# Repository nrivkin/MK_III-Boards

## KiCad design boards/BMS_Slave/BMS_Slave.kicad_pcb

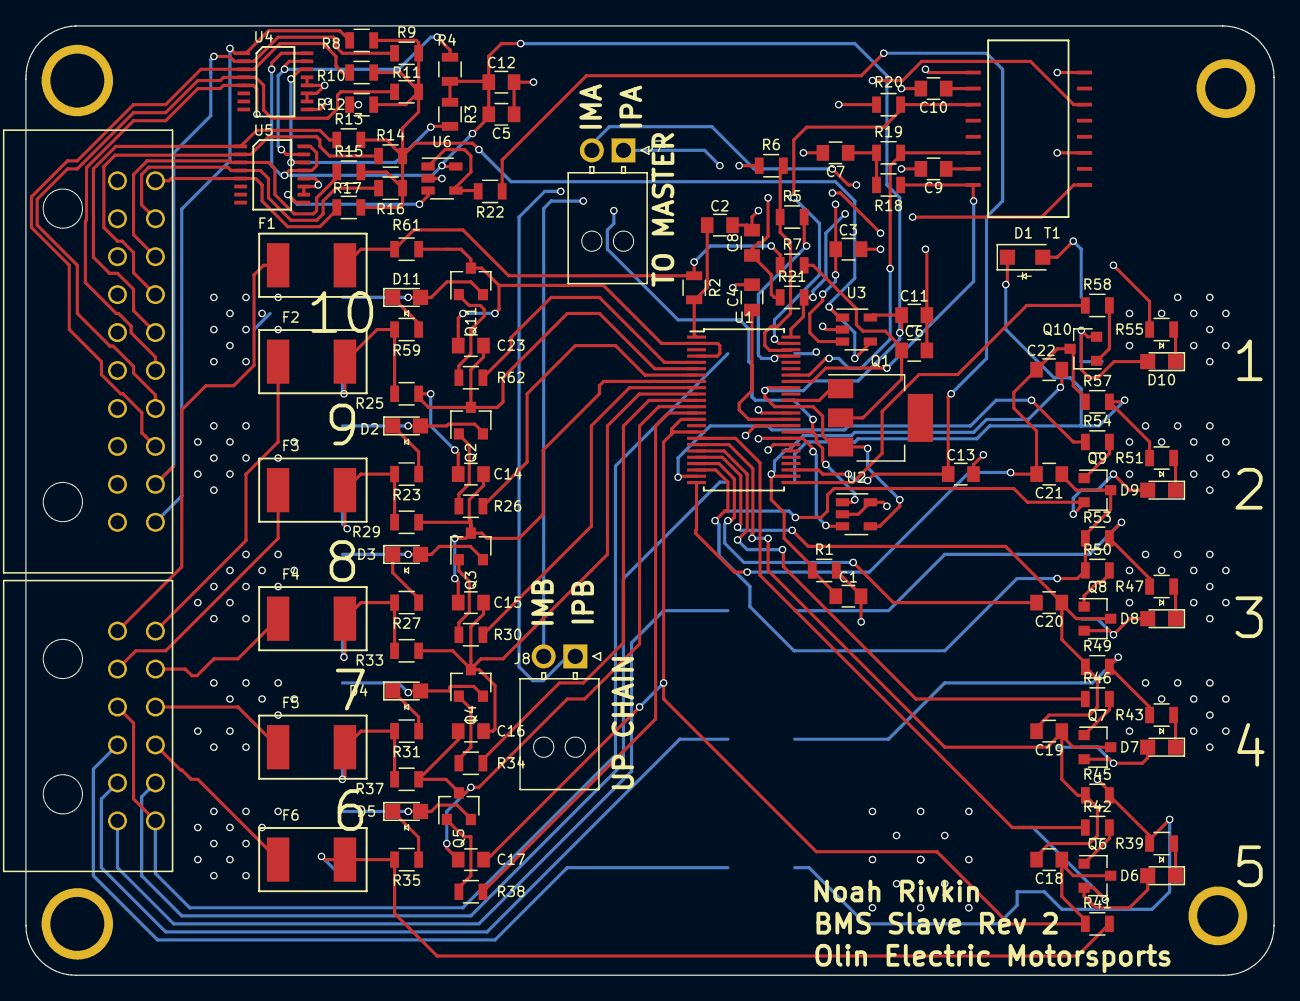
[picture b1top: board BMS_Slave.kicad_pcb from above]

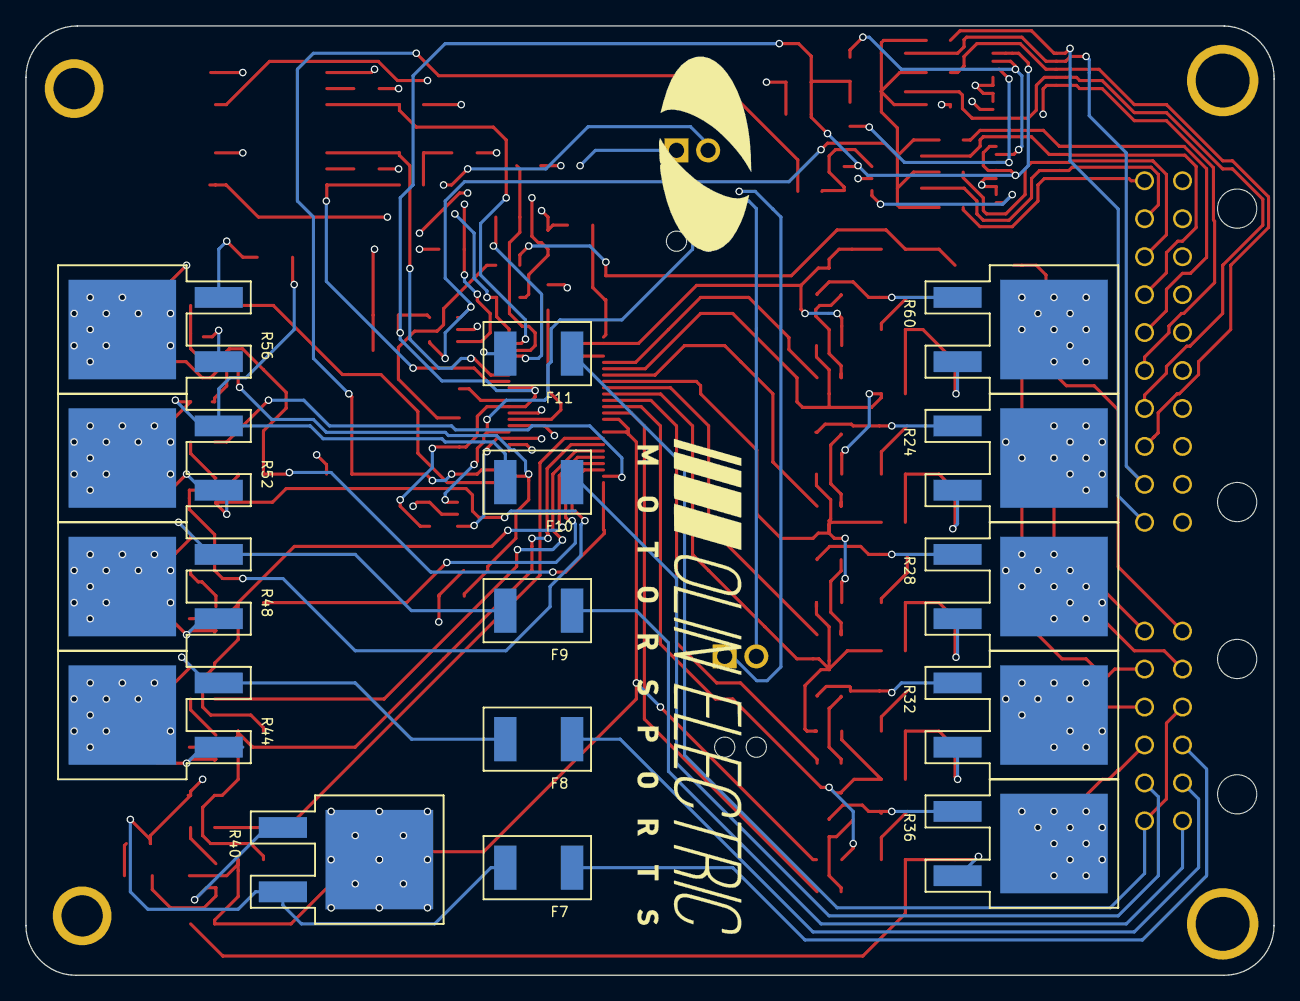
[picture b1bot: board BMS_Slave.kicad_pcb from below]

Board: 4 copper layers, 98.7 x 75.1 mm, 133 parts (15 on the bottom side), 109 nets.

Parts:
C1, C7, C8, C9, C10, C13, C14, C15, C16, C17, C18, C19, C20, C21, C22, C23: 10nF; C_0805_OEM
C2, C6: C_0.1uF; C_0805_OEM
C3, C4, C5, C11, C12: 1uF; C_0805_OEM
D1: D_Schottky_SOD123; D_SOD-123W_OEM
D2, D3, D4, D5, D6, D7, D8, D9, D10, D11: LED_0805; LED_0805_OEM
F1, F2, F3, F4, F5, F6, F7, F8, F9, F10, F11: 200mA_Fuse; Fuse_1812
J1, J3: Mounting_Hole_4-40
J2, J4: Mounting_Hole_4-40; Mounting_Hole_Insert_4-40
J5: MicroFit_12; Microfit3_Header_02x06_Angled_OEM
J6: MicroFit_20; Molex_Microfit3_Header_02x10_Angled_OEM
J7, J8: NanoFit_2; Molex_NanoFit_1x02x2.50mm_Angled_OEM
Q1: Q_NPN_BCE; SOT-223
Q2, Q3, Q4, Q5, Q6, Q7, Q8, Q9, Q10, Q11: NMOS_GSD_30V; SOT-23F
R1, R2, R7, R22, R25, R29, R33, R37, R41, R45, R49, R53, R57, R61: R_100; R_0805_OEM
R3, R4: 4.99k; R_0805_OEM
R5, R6: R_1k; R_0805_OEM
R8, R9, R10, R11, R12, R13, R14, R15, R16, R17: R_10k; R_0805_OEM
R18, R19, R20, R21: 60.4; R_0805_OEM
R23, R27, R31, R35, R39, R43, R47, R51, R55, R59: R_475; R_0805_OEM
R24, R28, R32, R36, R40, R44, R48, R52, R56, R60: DTO25
R26, R30, R34, R38, R42, R46, R50, R54, R58, R62: 3.3k; R_0805_OEM
T1: T_LAN_7490100111A; 7490100111A
U1: LTC6811-1; TSSOP-48_LTC6811-1
U2: 24AA01; SOT-23-5_OEM
U3, U6: MCP6001; SOT-23-5_OEM
U4, U5: LTC1380; SSOP-16_LTC1380

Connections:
/Balance1/CELL_SENSE: C21.2, C22.1, Q10.3, R57.1, U1.24
/Balance1/SENSE_BELOW: C1.1, C22.2, R1.1, U1.26
/Balance2/CELL_SENSE: C21.1, Q9.3, R50.1, R53.1, U1.22
/Balance2/V_BELOW: D1.1, F10.2, R51.2, R52.2, R57.2
/Balance3/CELL_SENSE: C19.2, C20.1, Q8.3, R49.1, U1.20
/Balance3/V_BELOW: F9.2, R47.2, R48.2, R53.2
/Balance4/CELL_SENSE: C18.2, C19.1, Q7.3, R45.1, U1.18
/Balance4/V_BELOW: F8.2, R43.2, R44.2, R49.2
/Balance5/CELL_SENSE: C17.2, C18.1, Q6.3, R41.1, U1.14, U1.16
/Balance5/V_BELOW: F7.2, R39.2, R40.2, R45.2
/Balance6/CELL_SENSE: C16.2, C17.1, Q5.3, R37.1, U1.12
/Balance6/V_BELOW: F6.2, R35.2, R36.2, R41.2
/Balance7/CELL_SENSE: C15.2, C16.1, Q4.3, R33.1, U1.10
/Balance7/V_BELOW: F5.2, R31.2, R32.2, R37.2
/Balance8/CELL_SENSE: C14.2, C15.1, Q3.3, R29.1, U1.8
/Balance8/V_BELOW: F4.2, R27.2, R28.2, R33.2
/Balance9/CELL_SENSE: C14.1, C23.2, Q2.3, R25.1, U1.6
/Balance9/V_BELOW: F3.2, R23.2, R24.2, R29.2
/Balance10/CELL_SENSE: C23.1, Q11.3, R61.1, U1.2, U1.4
/Balance10/V_BELOW: F2.2, R25.2, R59.2, R60.2
/Balance10/V_CELL: F1.2, R2.1, R7.1, R61.2
/CELL_TEMP1: J6.11, R8.1, U4.1
/CELL_TEMP2: J6.12, R9.1, U4.2
/CELL_TEMP3: J6.13, R10.1, U4.3
/CELL_TEMP4: J6.14, R11.1, U4.4
/CELL_TEMP5: J6.15, R12.1, U4.5
/CELL_TEMP6: J6.16, R13.1, U5.1
/CELL_TEMP7: J6.17, R14.1, U5.2
/CELL_TEMP8: J6.18, R15.1, U5.3
/CELL_TEMP9: J6.19, R16.1, U5.4
/CELL_TEMP10: J6.20, R17.1, U5.5
/Cell1: F10.1, J5.8
/Cell2: F9.1, J5.1
/Cell3: F8.1, J5.2
/Cell4: F7.1, J5.3
/Cell5: F6.1, J5.9
/Cell6: F5.1, J5.10
/Cell7: F4.1, J5.11
/Cell8: F3.1, J5.5
/Cell9: F2.1, J5.12
/Cell10: F1.1, J5.6
/Control1: R58.1, U1.25
/Control2: R54.1, U1.23
/Control3: C20.2, U1.21
/Control4: R46.1, U1.19
/Control5: R42.1, U1.17
/Control6: R38.1, U1.13
/Control7: R34.1, U1.11
/Control8: R30.1, U1.9
/Control9: R26.1, U1.7
/Control10: R62.1, U1.5
/GPIO1: C13.1, R22.1, U1.27
/LowSide: F11.1, J5.4, J5.7
/SCL: R4.2, U1.33, U2.1, U4.15, U5.15
/SDA: R3.2, U1.32, U2.3, U4.14, U5.14
/VREF2: R8.2, R9.2, R10.2, R11.2, R12.2, R13.2, R14.2, R15.2, R16.2, R17.2, U3.1, U3.4
/VREG: C5.1, C11.1, C12.1, Q1.3, R3.1, R4.1, U1.37, U1.40, U2.4, U3.5, U4.16, U5.13, U5.16, U6.5
GND: C1.2, C2.2, C3.2, C4.2, C5.2, C6.2, C7.2, C8.2, C9.2, C10.2, C11.2, C12.2, C13.2, D1.2, F11.2, J6.1, J6.2, J6.3, J6.4, J6.5, J6.6, J6.7, J6.8, J6.9, J6.10, R1.2, R6.1, R55.2, R56.2, U1.30, U1.31, U1.36, U2.2, U2.5, U3.2, U4.10, U4.11, U4.12, U4.13, U5.10, U5.11, U5.12, U6.2
unnamed: C2.1, R2.2, U1.1
unnamed: C3.1, U1.34, U3.3
unnamed: C4.1, U1.35
unnamed: C6.1, Q1.2, R7.2
unnamed: C7.1, R18.2, R19.1
unnamed: C8.1, R20.2, R21.1
unnamed: C9.1, T1.15
unnamed: C10.1, T1.10
unnamed: D2.1, R23.1
unnamed: D2.2, Q2.2, R24.3
unnamed: D3.1, R27.1
unnamed: D3.2, Q3.2, R28.3
unnamed: D4.1, R31.1
unnamed: D4.2, Q4.2, R32.3
unnamed: D5.1, R35.1
unnamed: D5.2, Q5.2, R36.3
unnamed: D6.1, R39.1
unnamed: D6.2, Q6.2, R40.3
unnamed: D7.1, R43.1
unnamed: D7.2, Q7.2, R44.3
unnamed: D8.1, R47.1
unnamed: D8.2, Q8.2, R48.3
unnamed: D9.1, R51.1
unnamed: D9.2, Q9.2, R52.3
unnamed: D10.1, R55.1
unnamed: D10.2, Q10.2, R56.3
unnamed: D11.1, R59.1
unnamed: D11.2, Q11.2, R60.3
unnamed: J7.1, T1.3
unnamed: J7.2, T1.1
unnamed: J8.1, T1.8
unnamed: J8.2, T1.6
unnamed: Q1.1, U1.38
unnamed: Q2.1, R26.2
unnamed: Q3.1, R30.2
unnamed: Q4.1, R34.2
unnamed: Q5.1, R38.2
unnamed: Q6.1, R42.2
unnamed: Q7.1, R46.2
unnamed: Q8.1, R50.2
unnamed: Q9.1, R54.2
unnamed: Q10.1, R58.2
unnamed: Q11.1, R62.2
unnamed: R5.1, R6.2, U1.46
unnamed: R5.2, U1.45
unnamed: R18.1, T1.16, U1.41
unnamed: R19.2, T1.14, U1.42
unnamed: R20.1, T1.11, U1.47
unnamed: R21.2, T1.9, U1.48
unnamed: R22.2, U6.1, U6.4
unnamed: U4.9, U5.9, U6.3

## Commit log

2018-05-11 Updating
